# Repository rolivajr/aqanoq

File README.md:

# aqanoq
Robotic Observatory Spaceapps Guatemala

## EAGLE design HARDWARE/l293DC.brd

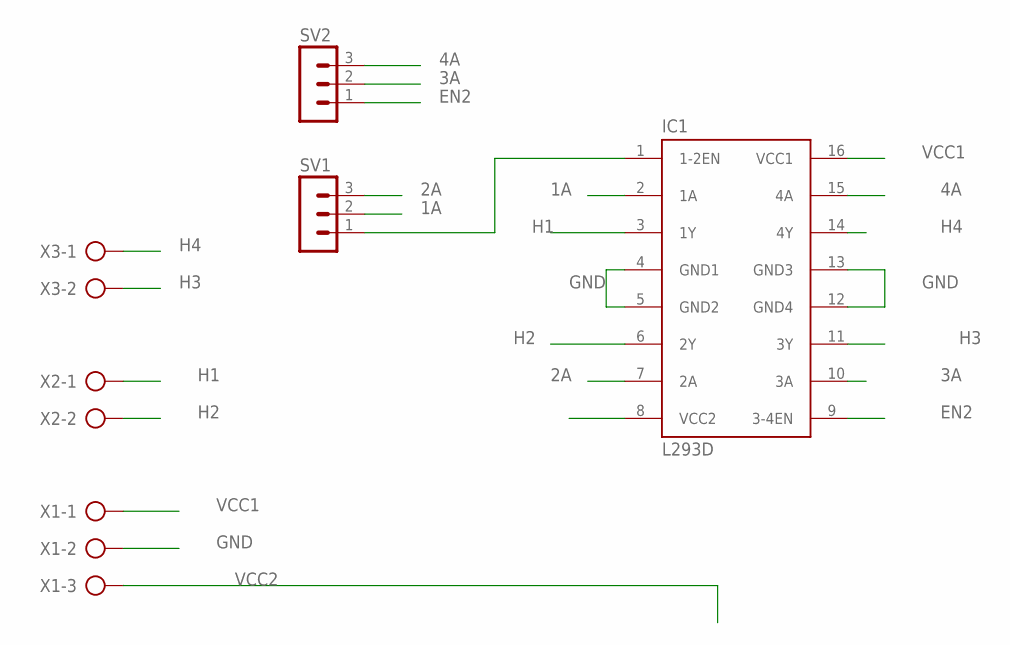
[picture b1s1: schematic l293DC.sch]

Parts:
IC1: L293D; DIL16
SV1, SV2: MA03-1
X1: AK500/3
X2, X3: AK500/2

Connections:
1A: IC1.2 (1A), SV1.2
2A: IC1.7 (2A), SV1.3
3A: IC1.10 (3A), SV2.2
4A: IC1.15 (4A), SV2.3
EN2: IC1.9 (3-4EN), SV2.1
GND: IC1.4 (GND1), IC1.5 (GND2), IC1.12 (GND4), IC1.13 (GND3), X1.2
H1: IC1.3 (1Y), X2.1
H2: IC1.6 (2Y), X2.2
H3: IC1.11 (3Y), X3.2
H4: IC1.14 (4Y), X3.1
unnamed: IC1.1 (1-2EN), SV1.1
VCC1: IC1.16 (VCC1), X1.1
VCC2: IC1.8 (VCC2), X1.3

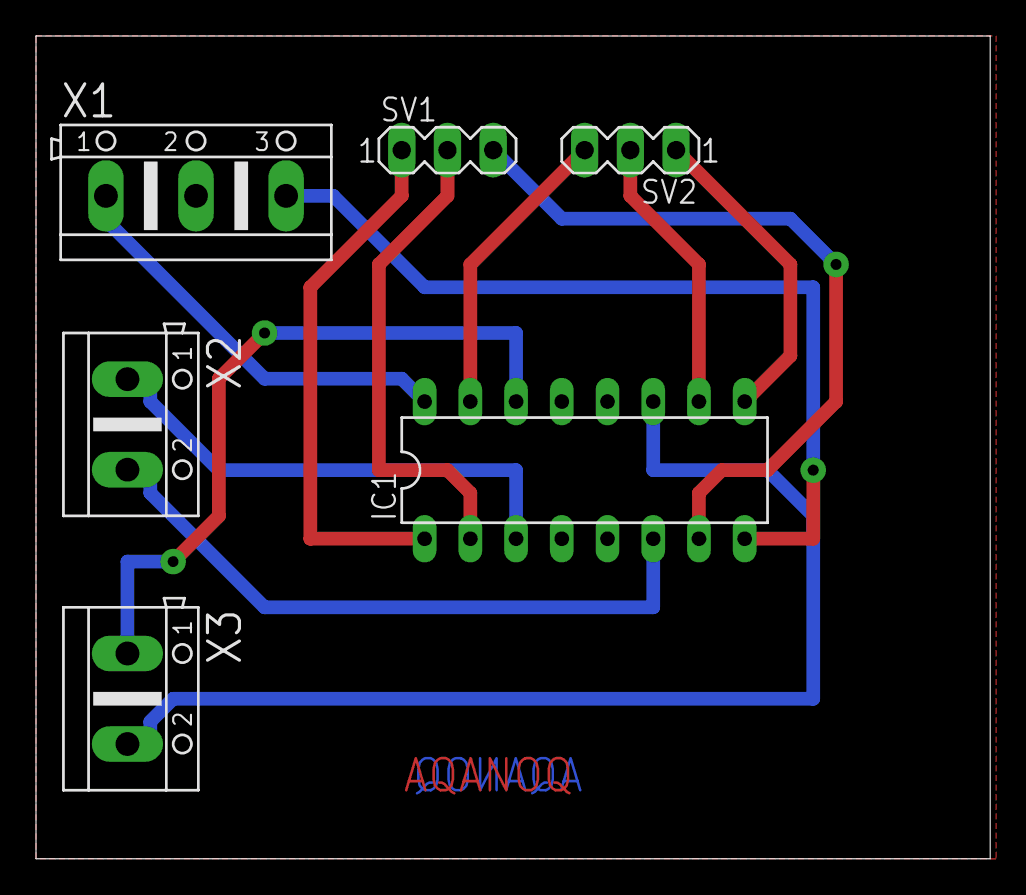
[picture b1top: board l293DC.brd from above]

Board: 2 copper layers, 53.0 x 45.7 mm, 6 parts (0 on the bottom side), 13 nets.

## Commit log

2015-04-19 SpaceApps1
2015-04-19 arduinoCode
2015-04-19 gears
2015-04-19 Sensors Info
2015-04-19 about
2015-04-19 Calculator
    Conversion between horizontal and equatorial systems
